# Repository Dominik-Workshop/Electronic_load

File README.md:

# DC Electronic load

### More info about this project can be found on my channel: 
 https://youtu.be/NScaRQj53l0

## Used tools:
 &nbsp;&nbsp;&nbsp;&nbsp; &nbsp;&nbsp;&nbsp;&nbsp; 
 &nbsp;&nbsp;&nbsp;&nbsp; &nbsp;&nbsp;&nbsp;&nbsp; 
 &nbsp;&nbsp; &nbsp;&nbsp;&nbsp;&nbsp; 

## Project status: :heavy_check_mark: ready for construction!
The project is poised for construction and operational use. However, ongoing development persists, addressing minor bug fixes and introducing new features. Stay tuned for updates!

## Project overview
Commercially available electronic loads often come with a hefty price tag, so I decided to build my own. 
This project was inspired by many electronic loads, with the primary inspiration being Scullcom's Electronic DC Load. You can view it [here](https://www.youtube.com/watch?v=9fsf1CgnTRk&list=PLUMG8JNssPPzbr4LydbTcBrhoPlemu5Dt&ab_channel=ScullcomHobbyElectronics).

&nbsp;&nbsp;&nbsp; 

### Project goals:
- **300 W power dissipation**

- **up to 8A and 50V** (obeying the 300W limit)

- **Remote voltage sensing option**

- **Easy to input values:** you can use an encoder as well as a keypad

- **5 modes of operation**
  - **Constant current mode**

  - **Constant power mode**

  - **Constant resistance mode**

  - **Transient response mode**

  - **Battery testing mode**

- **Nice to look at:** doesn't look like a poor DIY build

## Electronics:
### Block diagram

### PCBs:
- Main board: responsible for main funcionalities of the load

- Front board: responsible for user input with the rotary encoder and switching the voltage measurement circuitry between the main and sense terminals

## Mechanical construction:
The case for this project is made with 1mm thick bent sheet metal, with a 3D printed front panel.

## PC remote controll battery mode app
 
The app is currently available for Windows only. To run it, simply double-click on

`\desktop_app\release\windows-64bit\electronic_load_control_app.exe`

## Accuracy measurements
<details>
<summary>Click to learn more</summary>

The precision of the electronic load's current and voltage measurements, as well as its set current accuracy, were tested against the `Sanwa PC7000` multimeter. The following tables present the results of these measurements.

### Accuracy of set and measured current values

| Set Value [A] | Load Measurement [A] | Multimeter Measurement [A]  |
|:--------------|:---------------------|:----------------------------|
| 0.1           | 0.104                | 0.1032 ± 0.0029             |
| 0.2           | 0.203                | 0.2024 ± 0.0037             |
| 0.3           | 0.300                | 0.3000 ± 0.0044             |
| 0.4           | 0.406                | 0.4051 ± 0.0053             |
| 0.5           | 0.500                | 0.4997 ± 0.0060             |
| 0.6           | 0.602                | 0.6020 ± 0.0069             |
| 0.7           | 0.702                | 0.7020 ± 0.0077             |
| 0.8           | 0.800                | 0.8000 ± 0.0084             |
| 0.9           | 0.904                | 0.9038 ± 0.0093             |
| 1.0           | 1.007                | 1.0065 ± 0.0101             |
| 2.0           | 2.007                | 2.0070 ± 0.0181             |
| 3.0           | 3.006                | 3.0057 ± 0.0261             |
| 4.0           | 4.003                | 4.0022 ± 0.0341             |
| 5.0           | 5.002                | 5.0007 ± 0.0421             |
| 6.0           | 6.001                | 5.996 ± 0.068               |
| 7.0           | 6.998                | 6.997 ± 0.076               |
| 8.0           | 7.998                | 7.990 ± 0.084               |

### Accuracy of voltage measurements

| Load Measurement [V] | Multimeter Measurement [V] |
|:---------------------|:---------------------------|
| 1.002                | 1.0022 ± 0.0006            |
| 2.002                | 2.0029 ± 0.0009            |
| 3.004                | 3.0043 ± 0.0012            |
| 4.004                | 4.0039 ± 0.0015            |
| 5.006                | 5.0058 ± 0.0018            |
| 8.004                | 8.004 ± 0.006              |
| 10.01                | 10.007 ± 0.007             |
| 12.01                | 12.008 ± 0.007             |
| 14.01                | 14.010 ± 0.008             |
| 16.01                | 16.004 ± 0.009             |
| 18.01                | 18.007 ± 0.010             |
| 20.01                | 20.008 ± 0.011             |
| 25.01                | 25.011 ± 0.013             |
| 30.02                | 30.016 ± 0.015             |
| 35.02                | 35.019 ± 0.017             |
| 40.02                | 40.019 ± 0.019             |
| 45.02                | 45.023 ± 0.021             |
| 50.01                | 50.012 ± 0.023             |

### Conclusion: ✅

The current values measured by the electronic load did not deviate from the set value by more than **7 mA**. All measurements taken by the electronic load are within the range of values measured by the multimeter, considering the multimeter's measurement error.
</details>

## Uploading the code using USBASP
<details>
<summary>Click to learn more</summary>

Add the following code to the `platformio.ini` file

    upload_protocol = custom
    upload_port = usb
    upload_flags = 
        -C
        ${platformio.packages_dir}/tool-avrdude/avrdude.conf
        -p
        $BOARD_MCU
        -P
        $UPLOAD_PORT
        -c
        usbasp
    upload_command = avrdude $UPLOAD_FLAGS -U flash:w:$SOURCE:i

Uploading the code this way will reduce the boot up time.

**Note:** Since this method removes the bootloader, in order to program the uC via UART next time, you have to burn the bootloader.
</details>

## What could be improved in the next version:
  - Add reverse polarity protection
  - Higher resolution DAC

## Special thanks

Special thanks to [**Eryk Możdzeń**](https://github.com/Eryk-Mozdzen), who helped solving a software problem with a memory leak.

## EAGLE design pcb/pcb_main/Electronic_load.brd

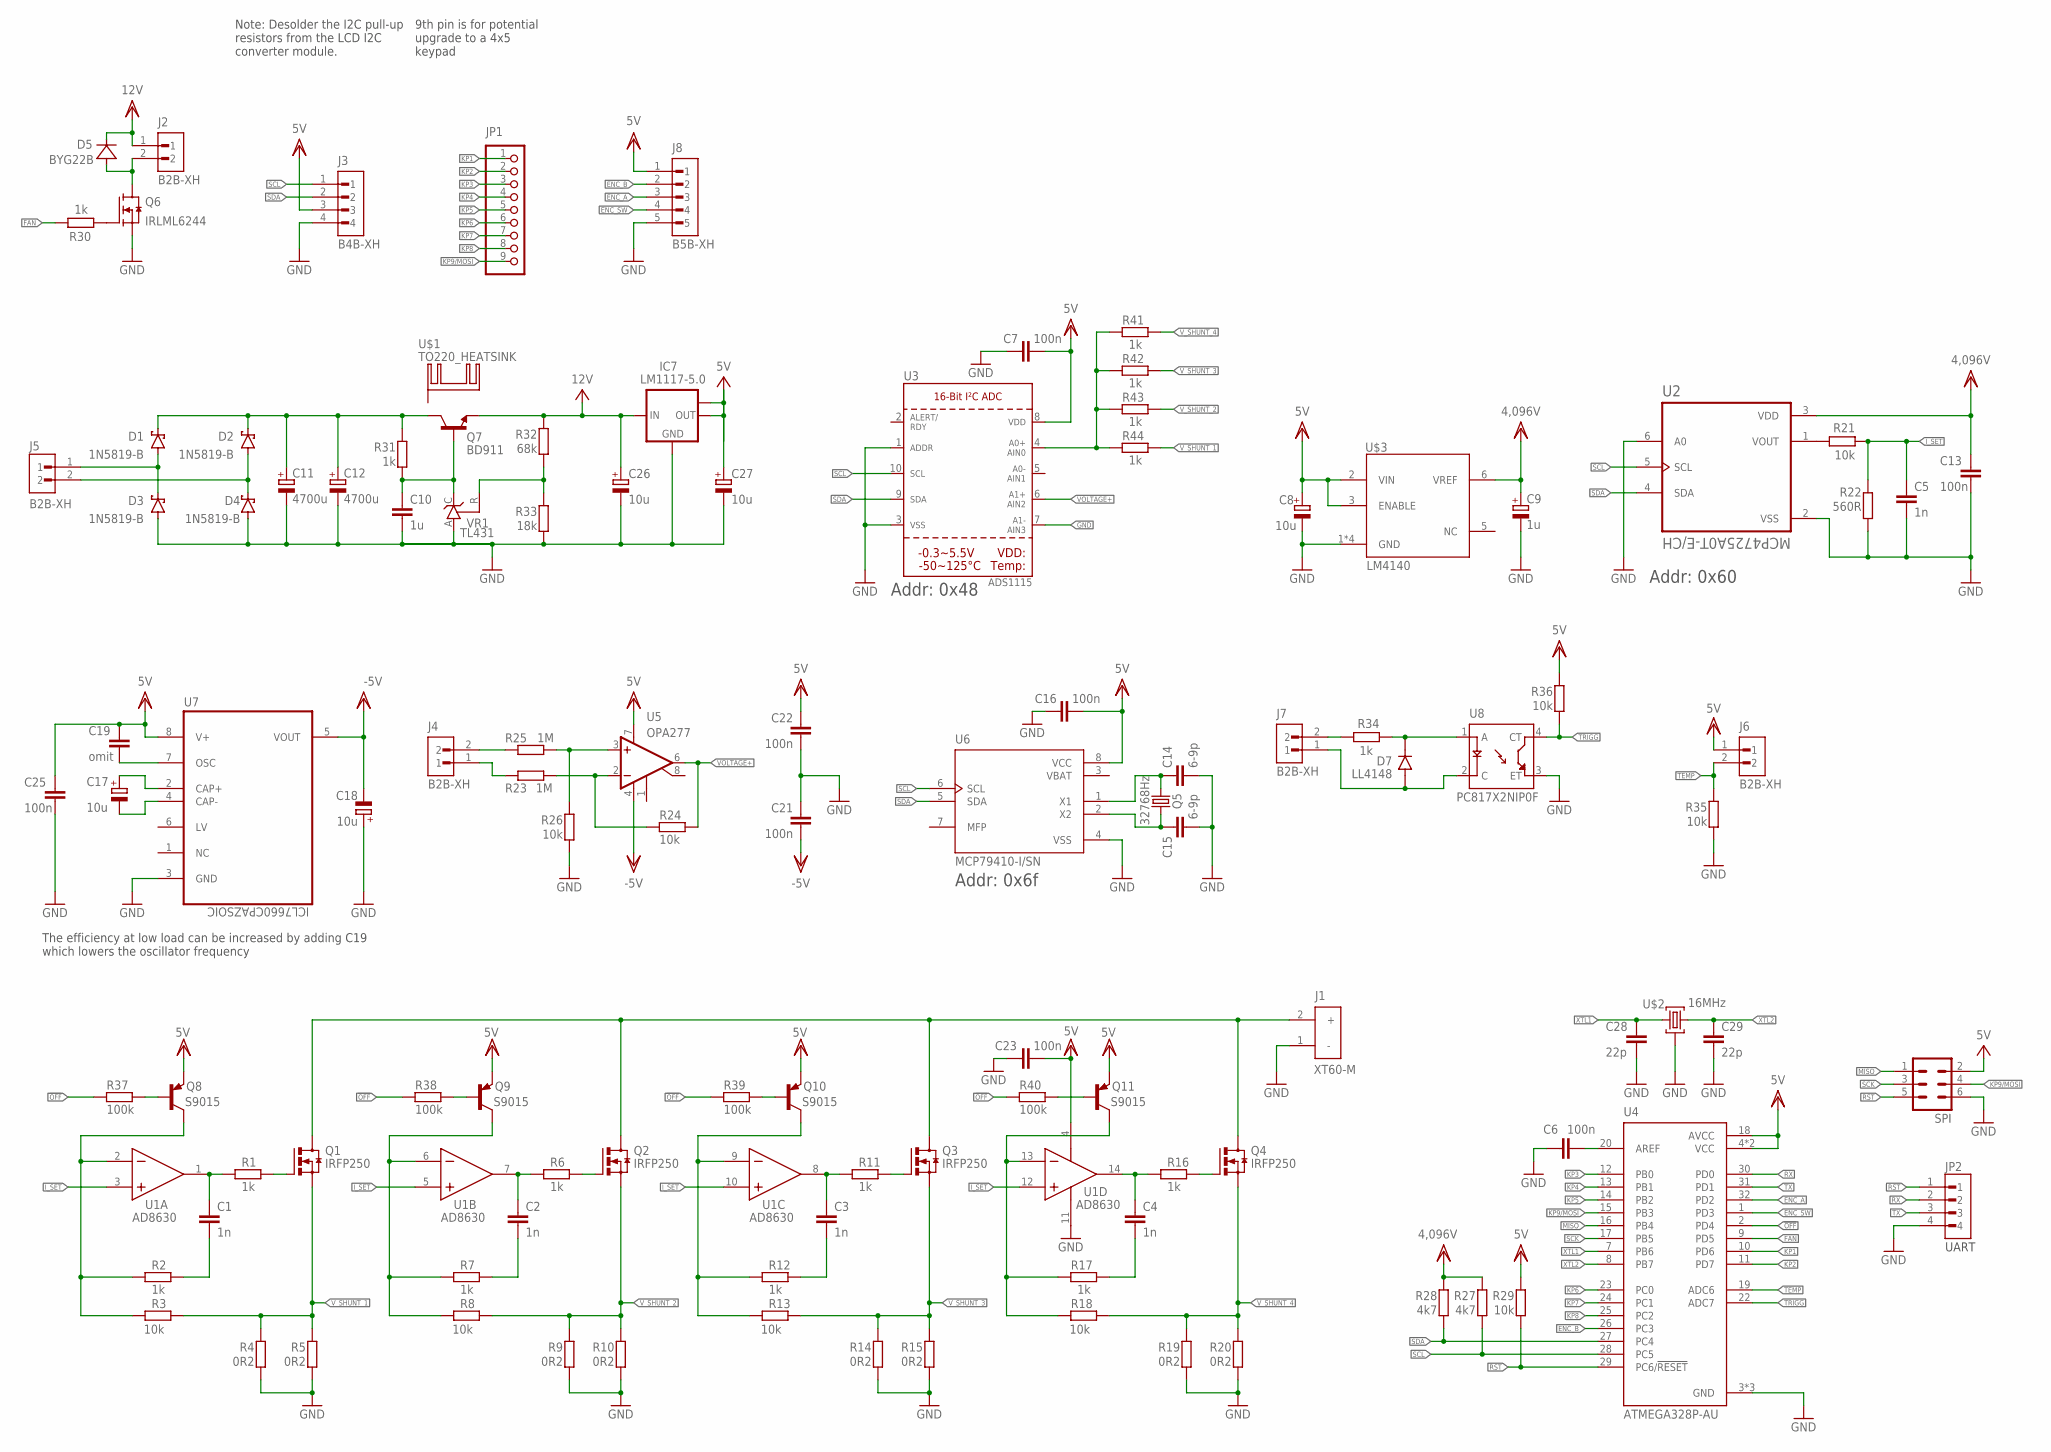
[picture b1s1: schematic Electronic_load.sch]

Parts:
C1, C2, C3, C4, C5: 1n; C0603
C6, C7, C13, C16, C21, C22, C25: 100n; C0603
C8, C17, C18: 10u; CT3528
C9: 1u; CT3216
C10: 1u; C0603
C11, C12: 4700u; E7,5-16
C14, C15: 6-9p; C0603
C19: omit; C0603
C23: 100n; C0603K
C26, C27: 10u; B/3528-21W
C28, C29: 22p; C0603
D1, D2, D3, D4: 1N5819-B; DO41-7.6
D5: BYG22B; DO-214AC
D7: LL4148; DIOMELF3515N
IC7: LM1117-5.0; SOT223
J1: XT60-M; AMASS_XT60-M
J2, J4, J5, J6, J7: B2B-XH; JST_B2B-XH-A(LF)(SN)
J3: B4B-XH; JST_B4B-XH-A(LF)(SN)
J8: B5B-XH; JST_B5B-XH-A(LF)(SN)
JP1: PINHD-1X9; 1X09
JP2: B4B-XH; JST_B4B-XH-A(LF)(SN)
Q1, Q2, Q3, Q4: IRFP250; TO-247AD-V
Q5: 32768Hz; TC26H
Q6: IRLML6244; SOT23
Q7: BD911; TO220V
Q8, Q9, Q10, Q11: S9015; SOT23
R1, R6, R11, R16, R31: 1k; R0805
R2, R7, R12, R17, R30, R34, R41, R42, R43, R44: 1k; R0603
R3, R8, R13, R18, R21, R24, R26, R29, R35, R36: 10k; R0603
R4, R5, R9, R10, R14, R15, R19, R20: 0R2; R4527
R22: 560R; R0603
R23, R25: 1M; R0603
R27, R28: 4k7; R0603
R32: 68k; R0603
R33: 18k; R0603
R37, R38, R39, R40: 100k; R0603
SPI: MA03-2
U1: ANALOG_DEVICES_AD8630ARZ-REEL7ANALOG_DEVICES_AD86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; ANALOG_DEVICES_AD8630ARZ-REEL7_0
U2: MCP4725A0T-E/CH; SOT95P270X145-6N
U3: ADS1115; MSOP10
U4: ATMEGA328P-AU; QFP80P900X900X120-32N
U5: OPA277; SOIC-08_150MIL
U6: MCP79410-I/SN; SOIC127P600X175-8N
U7: ICL7660CPAZSOIC; SOIC8
U8: PC817X2NIP0F; SOT254P975X400-4N
U$1: TO220_HEATSINK
U$2: 16MHz; CRYSTAL_3,4X2,7
U$3: LM4140; SOIC8
VR1: TL431; TO92-CLP

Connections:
4,096V: C9.+, C13.1, R27.1, R28.1, U2.3 (VDD), U$3.6 (VREF)
5V: C7.1, C8.+, C16.1, C19.1, C22.2, C23.1, C25.1, C27.+, IC7.2 (OUT), IC7.TAB (OUT1), J3.3, J6.1, J8.1, Q8.2 (E), Q9.2 (E), Q10.2 (E), Q11.2 (E), R29.1, R36.2, SPI.2, U1.4 (+V), U3.8 (VDD), U4.4 (VCC), U4.6 (VCC), U4.18 (AVCC), U5.7 (V+), U6.8 (VCC), U7.8 (V+), U$3.2 (VIN), U$3.3 (ENABLE)
12V: C26.+, D5.C, IC7.3 (IN), J2.1, Q7.3 (E), R32.1
16V: C11.+, C12.+, D1.C, D2.C, Q7.2 (C), R31.1
!OFF: R37.1, R38.1, R39.1, R40.1, U4.2 (PD4)
-5V: C18.-, C21.1, U5.4 (V-), U7.5 (VOUT)
AREF: C6.1, U4.20 (AREF)
BASE: C10.1, Q7.1 (B), R31.2, VR1.C
CURRENT: R41.1, R42.1, R43.1, R44.1, U3.4 (AIN0)
DAC_OUT: R21.2, U2.1 (VOUT)
ENC_A: J8.3, U4.32 (PD2)
ENC_B: J8.2, U4.26 (PC3)
ENC_SW: J8.4, U4.1 (PD3)
FAN: R30.1, U4.9 (PD5)
GND: C5.2, C6.2, C7.2, C8.-, C9.-, C10.2, C11.-, C12.-, C13.2, C14.2, C15.2, C16.2, C18.+, C21.2, C22.1, C23.2, C25.2, C26.-, C27.-, C28.2, C29.2, D3.A, D4.A, IC7.1 (GND), J1.1 (-), J3.4, J8.5, JP2.4, Q6.2 (S), R4.1, R5.1, R9.1, R10.1, R14.1, R15.1, R19.1, R20.1, R22.2, R26.1, R33.2, R35.1, SPI.6, U1.11 (-V), U2.2 (VSS), U2.6 (A0), U3.1 (ADDR), U3.3 (VSS), U3.7 (AIN3), U4.3 (GND), U4.5 (GND), U4.21 (GND), U6.4 (VSS), U7.3 (GND), U8.3 (ET), U$2.GND (2), U$2.GND2 (2), U$3.1 (GND), U$3.4 (GND), U$3.7 (GND), U$3.8 (GND), VR1.A
I_SET: C5.1, R21.1, R22.1, U1.3 (+IN_A), U1.5 (+IN_B), U1.10 (+IN_C), U1.12 (+IN_D)
KP1: JP1.1, U4.10 (PD6)
KP2: JP1.2, U4.11 (PD7)
KP3: JP1.3, U4.12 (PB0)
KP4: JP1.4, U4.13 (PB1)
KP5: JP1.5, U4.14 (PB2)
KP6: JP1.6, U4.23 (PC0)
KP7: JP1.7, U4.24 (PC1)
KP8: JP1.8, U4.25 (PC2)
KP9/MOSI: JP1.9, SPI.4, U4.15 (PB3)
MISO: SPI.1, U4.16 (PB4)
unnamed: D7.C (K), R34.1, U8.1 (A)
unnamed: R25.2, R26.2, U5.3 (+IN)
unnamed: C1.2, R2.2
unnamed: C1.1, R1.1, U1.1 (OUT_A)
unnamed: Q1.G, R1.2
unnamed: Q8.3 (C), R2.1, R3.2, U1.2 (-IN_A)
unnamed: J7.2, R34.2
unnamed: J1.2 (+), Q1.D, Q2.D, Q3.D, Q4.D
unnamed: C2.2, R7.2
unnamed: C2.1, R6.1, U1.7 (OUT_B)
unnamed: Q2.G, R6.2
unnamed: Q8.1 (B), R37.2
unnamed: Q9.3 (C), R7.1, R8.2, U1.6 (-IN_B)
unnamed: R23.2, R24.1, U5.2 (-IN)
unnamed: C3.2, R12.2
unnamed: C3.1, R11.1, U1.8 (OUT_C)
unnamed: Q3.G, R11.2
unnamed: Q10.3 (C), R12.1, R13.2, U1.9 (-IN_C)
unnamed: C4.2, R17.2
unnamed: C4.1, R16.1, U1.14 (OUT_D)
unnamed: Q4.G, R16.2
unnamed: Q11.3 (C), R17.1, R18.2, U1.13 (-IN_D)
unnamed: D5.A, J2.2, Q6.3 (D)
unnamed: J4.2, R25.1
unnamed: J4.1, R23.1
unnamed: D1.A, D3.C, J5.1
unnamed: D2.A, D4.C, J5.2
unnamed: Q6.1 (G), R30.2
unnamed: C17.+, U7.2 (CAP+)
unnamed: C17.-, U7.4 (CAP-)
unnamed: C14.1, Q5.2, U6.1 (X1)
unnamed: C15.1, Q5.1, U6.2 (X2)
unnamed: C19.2, U7.7 (OSC)
unnamed: Q9.1 (B), R38.2
unnamed: R32.2, R33.1, VR1.R
unnamed: Q10.1 (B), R39.2
unnamed: Q11.1 (B), R40.2
RST: JP2.1, R29.2, SPI.5, U4.29 (PC6/!RESET)
RX: JP2.2, U4.30 (PD0)
SCK: SPI.3, U4.17 (PB5)
SCL: J3.1, R27.2, U2.5 (SCL), U3.10 (SCL), U4.28 (PC5), U6.6 (SCL)
SDA: J3.2, R28.2, U2.4 (SDA), U3.9 (SDA), U4.27 (PC4), U6.5 (SDA)
TEMP: J6.2, R35.2, U4.19 (ADC6)
TRIGG: R36.1, U4.22 (ADC7), U8.4 (CT)
TX: JP2.3, U4.31 (PD1)
T_GND: D7.A, J7.1, U8.2 (C)
VBAT: U6.3 (VBAT)
VOLTAGE+: R24.2, U3.6 (AIN2), U5.6 (OUT)
V_SHUNT_1: Q1.S, R3.1, R4.2, R5.2, R44.2
V_SHUNT_2: Q2.S, R8.1, R9.2, R10.2, R43.2
V_SHUNT_3: Q3.S, R13.1, R14.2, R15.2, R42.2
V_SHUNT_4: Q4.S, R18.1, R19.2, R20.2, R41.2
XTL1: C28.1, U4.7 (PB6), U$2.CRST1 (1)
XTL2: C29.1, U4.8 (PB7), U$2.CRST2 (3)

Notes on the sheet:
Addr: 0x48
Addr: 0x60
Addr: 0x6f
The efficiency at low load can be increased by adding C19 which lowers the oscillator frequency
9th pin is for potential upgrade to a 4x5 keypad
UART
Note: Desolder the I2C pull-up resistors from the LCD I2C converter module.

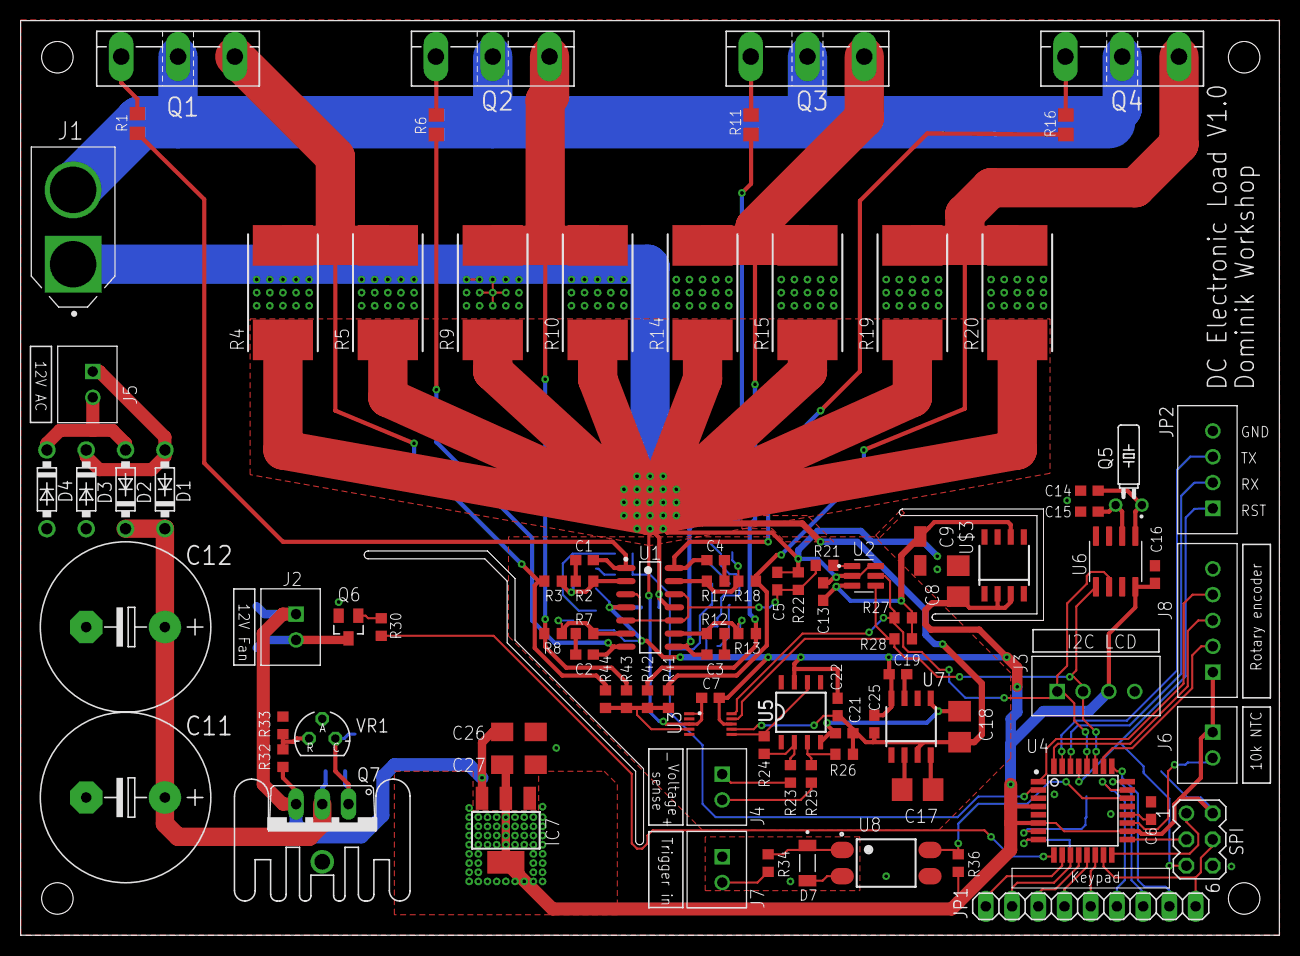
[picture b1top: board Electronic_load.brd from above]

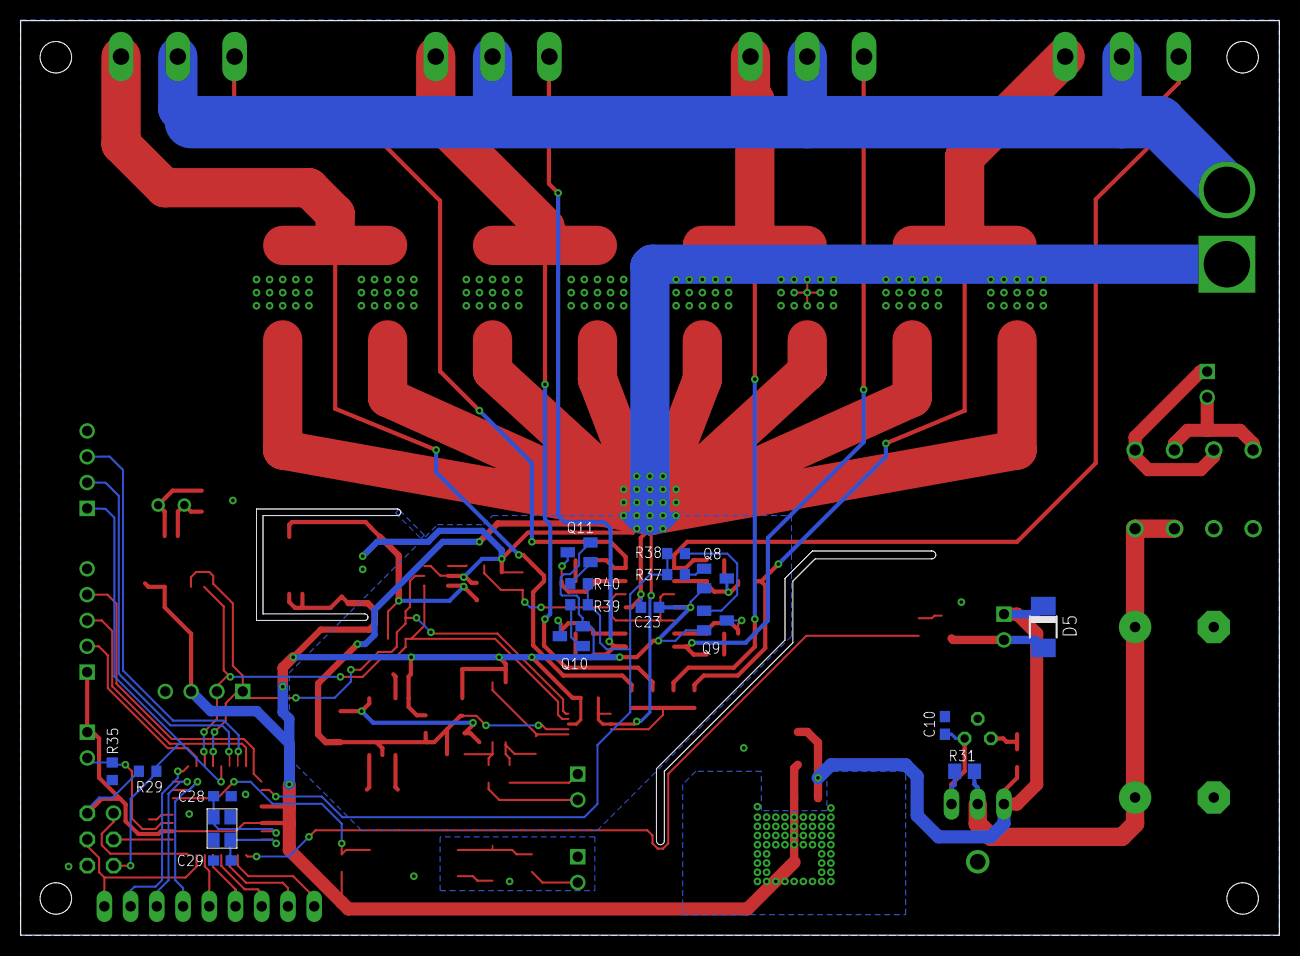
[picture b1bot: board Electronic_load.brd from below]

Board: 2 copper layers, 121.8 x 88.5 mm, 112 parts (17 on the bottom side), 79 nets.

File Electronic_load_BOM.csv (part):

"Part";"Value";"Device";"Package";"Description";"AMPLIFIERS_PER_PACKAGE";"AUTOMOTIVE_QUALIFIED";"AVAILABILITY";"CIIVA_IDS";"CODE__JEDEC";"COMPONENT_LINK_1_DESCRIPTION";"COMPONENT_LINK_1_URL";"COMPONENT_LINK_3_DESCRIPTION";"COMPONENT_LINK_3_URL";"DATASHEET";"DATASHEET_VERSION";"DESCRIPTION";"FOOTPRINT_VARIANT_NAME_0";"FOOTPRINT_VARIANT_NAME_1";"FOOTPRINT_VARIANT_NAME_2";"IMPORTED";"IMPORTED_FROM";"IMPORT_TS";"INPUT_BIAS_CURRENT";"INPUT_OFFSET_VOLTAGE";"IQ_AMP";"MF";"MOUNTING_TECHNOLOGY";"MP";"MPN";"OC_FARNELL";"OC_NEWARK";"PACKAGE";"PACKAGE_DESCRIPTION";"PACKAGE_VERSION";"POPULARITY";"PREFIX";"PRICE";"PURCHASE-URL";"RELEASE_DATE";"SLEW_RATE";"SMALL_SIGNAL_BANDWIDTH";"SPICEPREFIX";"VAULT_GUID";"VAULT_REVISION";"V_SPAN_MAX";"V_SPAN_MIN";
"C1";"1n";"C-EUC0603";"C0603";"CAPACITOR, European symbol";"";"";"";"";"";"";"";"";"";"";"";"";"";"";"";"";"";"";"";"";"";"";"";"";"";"";"";"";"";"";"73";"";"";"";"";"";"";"C";"";"";"";"";
"C2";"1n";"C-EUC0603";"C0603";"CAPACITOR, European symbol";"";"";"";"";"";"";"";"";"";"";"";"";"";"";"";"";"";"";"";"";"";"";"";"";"";"";"";"";"";"";"73";"";"";"";"";"";"";"C";"";"";"";"";
"C3";"1n";"C-EUC0603";"C0603";"CAPACITOR, European symbol";"";"";"";"";"";"";"";"";"";"";"";"";"";"";"";"";"";"";"";"";"";"";"";"";"";"";"";"";"";"";"73";"";"";"";"";"";"";"C";"";"";"";"";
"C4";"1n";"C-EUC0603";"C0603";"CAPACITOR, European symbol";"";"";"";"";"";"";"";"";"";"";"";"";"";"";"";"";"";"";"";"";"";"";"";"";"";"";"";"";"";"";"73";"";"";"";"";"";"";"C";"";"";"";"";
"C5";"1n";"C-EUC0603";"C0603";"CAPACITOR, European symbol";"";"";"";"";"";"";"";"";"";"";"";"";"";"";"";"";"";"";"";"";"";"";"";"";"";"";"";"";"";"";"73";"";"";"";"";"";"";"C";"";"";"";"";
"C6";"100n";"C-EUC0603";"C0603";"CAPACITOR, European symbol";"";"";"";"";"";"";"";"";"";"";"";"";"";"";"";"";"";"";"";"";"";"";"";"";"";"";"";"";"";"";"73";"";"";"";"";"";"";"C";"";"";"";"";
"C7";"100n";"C-EUC0603";"C0603";"CAPACITOR, European symbol";"";"";"";"";"";"";"";"";"";"";"";"";"";"";"";"";"";"";"";"";"";"";"";"";"";"";"";"";"";"";"73";"";"";"";"";"";"";"C";"";"";"";"";
"C8";"10u";"CPOL-EUCT3528";"CT3528";"POLARIZED CAPACITOR, European symbol";"";"";"";"";"";"";"";"";"";"";"";"";"";"";"";"";"";"";"";"";"";"";"";"";"";"";"";"";"";"";"1";"";"";"";"";"";"";"C";"";"";"";"";
"C9";"1u";"CPOL-EUCT3216";"CT3216";"POLARIZED CAPACITOR, European symbol";"";"";"";"";"";"";"";"";"";"";"";"";"";"";"";"";"";"";"";"";"";"";"";"";"";"";"";"";"";"";"1";"";"";"";"";"";"";"C";"";"";"";"";
"C10";"1u";"C-EUC0603";"C0603";"CAPACITOR, European symbol";"";"";"";"";"";"";"";"";"";"";"";"";"";"";"";"";"";"";"";"";"";"";"";"";"";"";"";"";"";"";"73";"";"";"";"";"";"";"C";"";"";"";"";
"C11";"4700u";"CPOL-EUE7.5-16";"E7,5-16";"POLARIZED CAPACITOR, European symbol";"";"";"";"";"";"";"";"";"";"";"";"";"";"";"";"";"";"";"";"";"";"";"";"";"";"";"";"";"";"";"4";"";"";"";"";"";"";"C";"";"";"";"";
"C12";"4700u";"CPOL-EUE7.5-16";"E7,5-16";"POLARIZED CAPACITOR, European symbol";"";"";"";"";"";"";"";"";"";"";"";"";"";"";"";"";"";"";"";"";"";"";"";"";"";"";"";"";"";"";"4";"";"";"";"";"";"";"C";"";"";"";"";
"C13";"100n";"C-EUC0603";"C0603";"CAPACITOR, European symbol";"";"";"";"";"";"";"";"";"";"";"";"";"";"";"";"";"";"";"";"";"";"";"";"";"";"";"";"";"";"";"73";"";"";"";"";"";"";"C";"";"";"";"";
"C14";"6-9p";"C-EUC0603";"C0603";"CAPACITOR, European symbol";"";"";"";"";"";"";"";"";"";"";"";"";"";"";"";"";"";"";"";"";"";"";"";"";"";"";"";"";"";"";"73";"";"";"";"";"";"";"C";"";"";"";"";
"C15";"6-9p";"C-EUC0603";"C0603";"CAPACITOR, European symbol";"";"";"";"";"";"";"";"";"";"";"";"";"";"";"";"";"";"";"";"";"";"";"";"";"";"";"";"";"";"";"73";"";"";"";"";"";"";"C";"";"";"";"";
"C16";"100n";"C-EUC0603";"C0603";"CAPACITOR, European symbol";"";"";"";"";"";"";"";"";"";"";"";"";"";"";"";"";"";"";"";"";"";"";"";"";"";"";"";"";"";"";"73";"";"";"";"";"";"";"C";"";"";"";"";
"C17";"10u";"CPOL-EUCT3528";"CT3528";"POLARIZED CAPACITOR, European symbol";"";"";"";"";"";"";"";"";"";"";"";"";"";"";"";"";"";"";"";"";"";"";"";"";"";"";"";"";"";"";"1";"";"";"";"";"";"";"C";"";"";"";"";
"C18";"10u";"CPOL-EUCT3528";"CT3528";"POLARIZED CAPACITOR, European symbol";"";"";"";"";"";"";"";"";"";"";"";"";"";"";"";"";"";"";"";"";"";"";"";"";"";"";"";"";"";"";"1";"";"";"";"";"";"";"C";"";"";"";"";
"C19";"omit";"C-EUC0603";"C0603";"CAPACITOR, European symbol";"";"";"";"";"";"";"";"";"";"";"";"";"";"";"";"";"";"";"";"";"";"";"";"";"";"";"";"";"";"";"73";"";"";"";"";"";"";"C";"";"";"";"";
"C21";"100n";"C-EUC0603";"C0603";"CAPACITOR, European symbol";"";"";"";"";"";"";"";"";"";"";"";"";"";"";"";"";"";"";"";"";"";"";"";"";"";"";"";"";"";"";"73";"";"";"";"";"";"";"C";"";"";"";"";
"C22";"100n";"C-EUC0603";"C0603";"CAPACITOR, European symbol";"";"";"";"";"";"";"";"";"";"";"";"";"";"";"";"";"";"";"";"";"";"";"";"";"";"";"";"";"";"";"73";"";"";"";"";"";"";"C";"";"";"";"";
"C23";"100n";"C-EUC0603K";"C0603K";"CAPACITOR, European symbol";"";"";"";"";"";"";"";"";"";"";"";"";"";"";"";"";"";"";"";"";"";"";"";"";"";"";"";"";"";"";"30";"";"";"";"";"";"";"C";"";"";"";"";
"C25";"100n";"C-EUC0603";"C0603";"CAPACITOR, European symbol";"";"";"";"";"";"";"";"";"";"";"";"";"";"";"";"";"";"";"";"";"";"";"";"";"";"";"";"";"";"";"73";"";"";"";"";"";"";"C";"";"";"";"";
"C26";"10u";"CPOL-EUB/3528-21W";"B/3528-21W";"POLARIZED CAPACITOR, European symbol";"";"";"";"";"";"";"";"";"";"";"";"";"";"";"";"";"";"";"";"";"";"";"";"";"";"";"";"";"";"";"4";"";"";"";"";"";"";"C";"";"";"";"";
"C27";"10u";"CPOL-EUB/3528-21W";"B/3528-21W";"POLARIZED CAPACITOR, European symbol";"";"";"";"";"";"";"";"";"";"";"";"";"";"";"";"";"";"";"";"";"";"";"";"";"";"";"";"";"";"";"4";"";"";"";"";"";"";"C";"";"";"";"";
"C28";"22p";"C-EUC0603";"C0603";"CAPACITOR, European symbol";"";"";"";"";"";"";"";"";"";"";"";"";"";"";"";"";"";"";"";"";"";"";"";"";"";"";"";"";"";"";"73";"";"";"";"";"";"";"C";"";"";"";"";
"C29";"22p";"C-EUC0603";"C0603";"CAPACITOR, European symbol";"";"";"";"";"";"";"";"";"";"";"";"";"";"";"";"";"";"";"";"";"";"";"";"";"";"";"";"";"";"";"73";"";"";"";"";"";"";"C";"";"";"";"";
"D1";"1N5819-B";"1N5819-B";"DO41-7.6";"1.0A SCHOTTKY BARRIER RECTIFIER";"";"";"";"";"";"";"";"";"";"";"";"";"";"";"";"";"";"";"";"";"";"";"";"";"";"";"";"";"";"";"11";"";"";"";"";"";"";"";"";"";"";"";
"D2";"1N5819-B";"1N5819-B";"DO41-7.6";"1.0A SCHOTTKY BARRIER RECTIFIER";"";"";"";"";"";"";"";"";"";"";"";"";"";"";"";"";"";"";"";"";"";"";"";"";"";"";"";"";"";"";"11";"";"";"";"";"";"";"";"";"";"";"";
"D3";"1N5819-B";"1N5819-B";"DO41-7.6";"1.0A SCHOTTKY BARRIER RECTIFIER";"";"";"";"";"";"";"";"";"";"";"";"";"";"";"";"";"";"";"";"";"";"";"";"";"";"";"";"";"";"";"11";"";"";"";"";"";"";"";"";"";"";"";
"D4";"1N5819-B";"1N5819-B";"DO41-7.6";"1.0A SCHOTTKY BARRIER RECTIFIER";"";"";"";"";"";"";"";"";"";"";"";"";"";"";"";"";"";"";"";"";"";"";"";"";"";"";"";"";"";"";"11";"";"";"";"";"";"";"";"";"";"";"";
"D5";"BYG22B";"BYG22B";"DO-214AC";"";"";"";"";"";"";"";"";"";"";"";"";"";"";"";"";"";"";"";"";"";"";"";"";"";"";"";"";"";"";"";"";"";"";"";"";"";"";"";"";"";"";"";
"D7";"LL4148";"LL4148";"DIOMELF3515N";"Check availability";"";"";"In Stock";"";"";"";"";"";"";"";"";" MMELF, 100V, 0.15A, Switching Diode & Array ";"";"";"";"";"";"";"";"";"";"Taiwan Semiconductor";"";"LL4148 L1";"";"";"";"MINI MELF-2 Taiwan Semiconductor";"";"";"";"";"None";"https://pricing.snapeda.com/search/part/LL4148 L1/?ref=eda";"";"";"";"";"";"";"";"";
"IC7";"LM1117IMPX-5.0";"LM1117IMPX-5.0";"SOT223";"";"";"";"";"";"";"";"";"";"";"";"";"";"";"";"";"";"";"";"";"";"";"";"";"";"";"";"";"";"";"";"";"";"";"";"";"";"";"";"";"";"";"";
"J1";"XT60-M";"XT60-M";"AMASS_XT60-M";"DC supply; XT60; male; PIN:2; for cable; soldered; 60A; 500V Check availability";"";"";"Not in stock";"";"";"";"";"";"";"";"";" Plug";" DC supply";" XT60";" male";" PIN: 2";" for cable";" soldered";" 30A";" 500V ";"";"";"";"";"";"";"";"";"";"AMASS";"";"XT60-M";"";"";"";"Package ";"";"";"";"";"None";"";
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
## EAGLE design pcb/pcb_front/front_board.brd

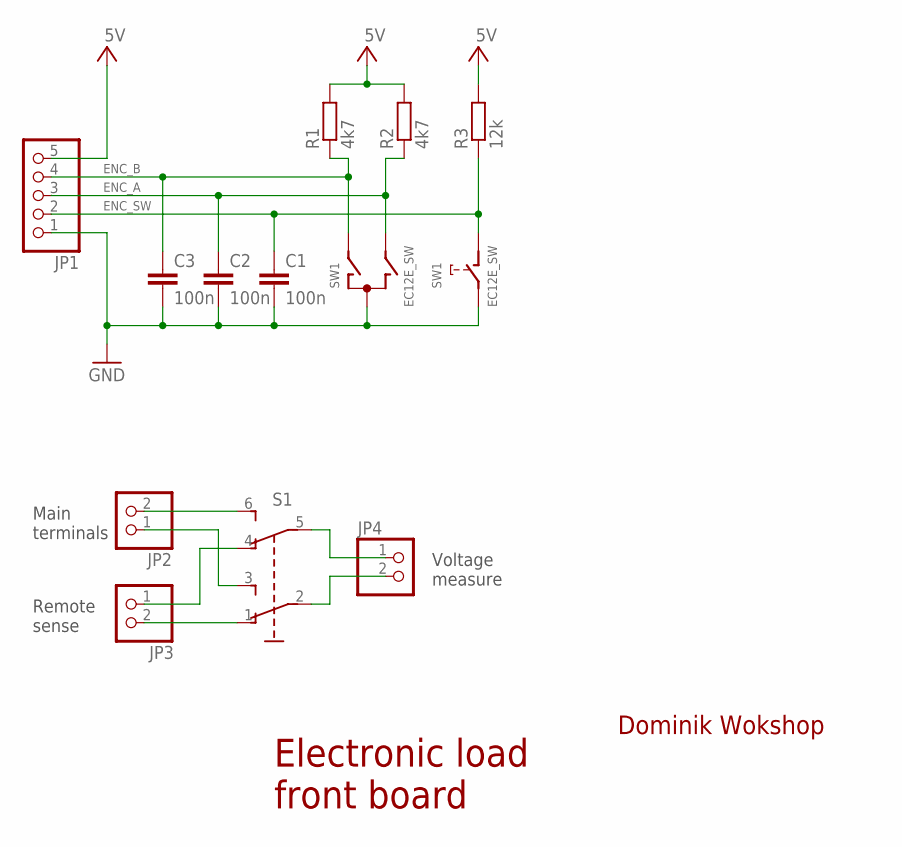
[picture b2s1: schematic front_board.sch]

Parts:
C1, C2, C3: 100n; C0603
JP1: PINHD-1X5/90; 1X05/90
JP2, JP3, JP4: PINHD-1X2/90; 1X02/90
R1, R2: 4k7; R0603
R3: 12k; R0603
S1: TL46PO; TL4XPO
SW1: EC12E_SW; ALPS_EC12E_SW

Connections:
5V: JP1.5, R1.2, R2.2, R3.2
ENC_A: C2.1, JP1.3, R2.1, SW1.B
ENC_B: C3.1, JP1.4, R1.1, SW1.A
ENC_SW: C1.1, JP1.2, R3.1, SW1.D (1)
GND: C1.2, C2.2, C3.2, JP1.1, SW1.C, SW1.E (2)
unnamed: JP4.2, S1.2
unnamed: JP3.2, S1.1 (O)
unnamed: JP4.1, S1.5 (P1)
unnamed: JP3.1, S1.4 (O1)
unnamed: JP2.1, S1.3 (S)
unnamed: JP2.2, S1.6 (S1)

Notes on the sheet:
Remote sense
Main terminals
Voltage measure
Electronic load front board
Dominik Wokshop

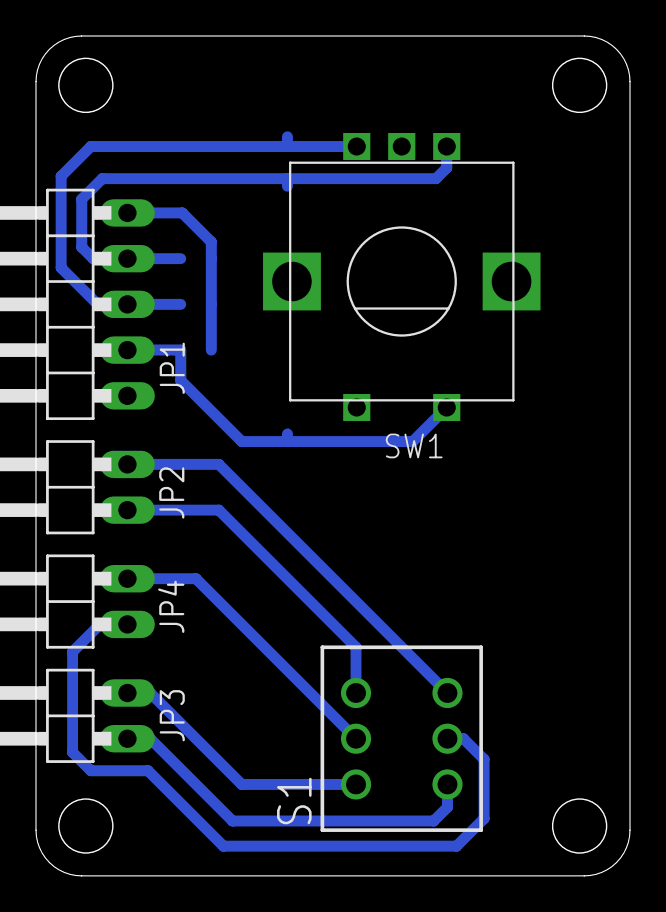
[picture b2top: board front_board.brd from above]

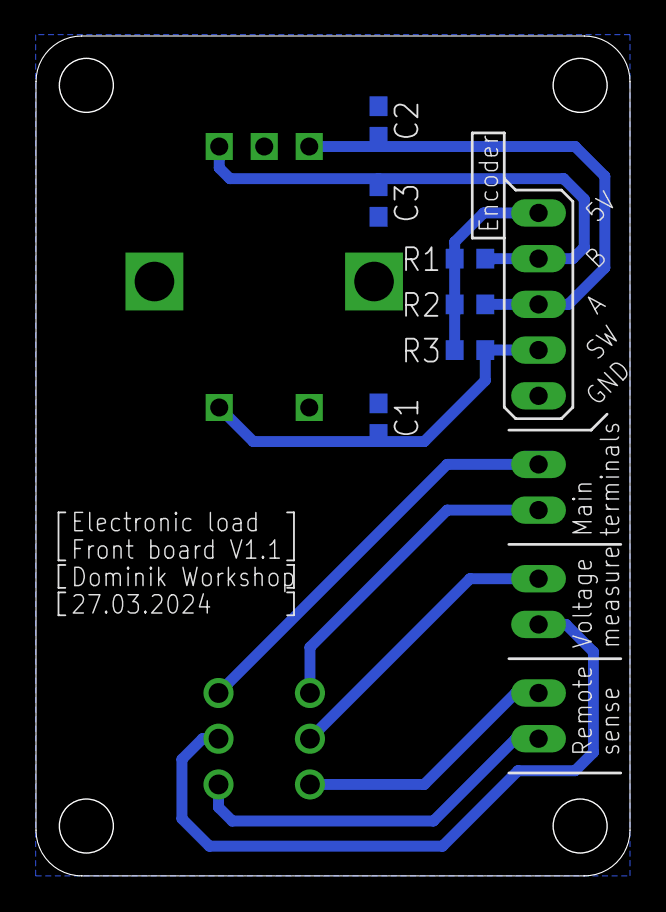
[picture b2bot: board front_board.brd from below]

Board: 2 copper layers, 32.9 x 46.6 mm, 12 parts (6 on the bottom side), 11 nets.

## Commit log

2022-07-12 datasheets
2022-07-12 VS Code initial commit
2022-07-12 ignore json
2022-07-12 most analog circutry done
2022-07-24 Power supply schematic done
2022-07-24 Most ICs
2022-07-24 Eagle trash
2022-07-24 Atmega pinout
2022-07-27 programming protocol via usbasp
2022-07-27 init function - pinMode
2022-07-27 calibration class and methods
2022-07-27 definition od pins and addresses
2022-07-27 initialized adc, dac, lcd, declared calValues
2022-07-27 finished power supply, added keypad, programming connector, transient trigger and more
2022-07-28 before voltage reference change
2022-07-29 new voltage reference
2022-07-31 finished V1.0
2022-07-31 added missing 3d models
2022-08-01 thermistor temperature measurement
2022-08-01 keypad, encoder, and thermistor
2022-08-01 encoder v1
2022-08-01 encoder init
2022-08-01 temperature and encoder test
2022-08-01 removed endoder init part
2022-08-01 encoder class with interrupt
2022-08-01 new encoder class tested
2022-08-01 methods definitions moved to source file
2022-08-01 9 pin keypad
2022-08-02 added encoder button
2022-08-02 encoder rotation and button tested
2022-08-03 keypad works
2022-08-04 finished V1
2022-08-05 new parts list
2022-08-05 added missing component values
2022-08-05 change value with encoder after key press
2022-08-05 degree and ohm custom character
2022-08-05 input value with decimal point from keypad
2022-08-05 fixed typo
2022-08-05 more comments
2022-08-05 user input class
2022-08-05 4 spaces -> 2 spaces indententions
2022-08-06 UserInput containing encoder and keypad
2022-08-06 seperate set variables, removed encoder and keypad
2022-08-06 enum with custom key names
2022-08-06 fixed some input bugs
2022-08-06 Encoder and Keypad separated from UserInput
2022-08-07 seperate function inputFromKeypad
2022-08-07 encoder switches decimal places
2022-08-07 display cursor pos (in resistance mode)
2022-08-07 UML diagram
2022-08-08 moving average filter
2022-08-08 constResistance new setting range
2022-08-08 all seems to work
2022-08-08 SetValue class
2022-08-08 max min value moved to private
2022-08-08 added values in description
2022-08-08 constPower and constResistance value input working
2022-08-09 removed numbers[] array
2022-08-09 minor imrovements
2022-08-17 added/corrected comments
2022-08-17 corrected comment
2022-08-19 changed encoder pin for pcb
2022-08-19 reversed encoder rotation
2022-08-19 changed for pcb
2022-08-20 datasheets update
2022-08-20 changed some resistor values
2022-08-23 cleaned up schematic
2022-08-28 License added
2022-08-29 test image
2022-08-29 first readme
2022-08-29 corrected image path
2022-08-29 rename folder
2022-08-29 renamed folder
2022-08-29 passed adc, dac objects
2022-08-29 template
2022-08-29 separate function for displaying the menu
2022-08-29 program via uart
2022-08-29 renders from fusion
2022-08-29 programming guidelines
2022-08-29 unfinished
2022-08-29 mount fits
2022-08-31 finished v1 printed
2022-09-02 painted and front finished
2022-09-02 height and holes adjusted
2022-09-02 project goals and to-do
2022-09-05 measurements work
2022-09-05 measurements in cons resistance
2022-09-05 updated to-do
2022-09-05 added comments
2022-09-06 lines counter
2022-09-06 none of the enums are zero
2022-09-06 decimal places enum
2022-09-06 CC mode, on/off, decimals enum
2022-09-06 on/off
2022-09-06 set current added
2022-09-06 dynamically change gain
2022-09-08 temperature moved to measurements
2022-09-08 temperature, calibration
2022-09-08 calibration, fan controll
2022-09-08 separate class for adc and dac calibration
2022-09-08 calibration, measurements
2022-09-08 offset current calibration
2022-09-08 getters and setters
2022-09-08 change displayed power precision >=100W
2022-09-08 zero current when off, (getters setters cal)
2022-09-08 more documentation, fanThreshold removed
2022-09-08 small renaming, dac getter setter
2022-09-08 EEPROM adresses renamed
2022-09-08 fan control, on/off
2022-09-09 enum min/max_decimal_place
2022-09-09 remove num_of_readings for mvng_average
2022-09-09 checkEncoder(), controlls
2022-09-09 adc moved to measurements
2022-09-09 controls class, power and resistance mode working
2022-09-09 load off on power up
2022-09-09 crude dac calibration
2022-09-09 dac offset cal
2022-09-09 description update
2022-09-09 timer library
2022-09-09 timer added
2022-09-09 cal, timer test
2022-09-09 current sink adjusted to new voltage divider
2022-09-09 power limiting test
2022-09-09 removed voltage parameter passed to functions
2022-09-09 removed measurements passed as parameter
2022-09-09 max values defines
2022-09-09 4mA min current
2022-09-09 dac offset calibration
2022-09-09 zero out current and power when load off
2022-09-10 update to-do, minor changes
2022-09-10 next version idea
2022-09-10 button debounce
2022-09-10 task loop
2022-09-10 documentation and clean up
2022-09-10 update readings when enetering via keypad
2022-09-11 minor changes
2022-09-11 rename current, power, resistance regulation func
2022-09-11 limit dacControll range, documentation
2022-09-11 documentation
2022-09-11 calibration finished
2022-09-11 clean up completed
2022-09-11 voltage with 3 decimals <10V
2022-09-12 began working on battery mode
2022-09-17 inputFromKeypad as userInput method works better
2022-09-18 checkEncoder as a method in userInput
2022-09-25 rotation doesn't print to lcd
2022-09-25 battery mode timer, encoder rotoration works
2022-09-25 added measured voltage offset calibration
2022-09-25 checkEncoder description
2022-09-25 keypad works in battery mode
2022-09-26 battery capacity measurement works
2022-09-26 cutoff edit, display capacity method
2022-09-27 cutoff works in battery mode
2022-09-27 capacity considering changes in current
2022-10-01 menu in void loop()
2022-10-01 debug2
2022-10-01 finally boots up
2022-10-01 doesn't run
2022-10-01 fix leak task
2022-10-01 int main() works
2022-10-01 works without void setup() and loop()
2022-10-01 FIXED MEMORY LEAK!!!!
2022-10-01 cleanup after debug and fix memory leak
2022-10-01 task done fix memory leak
2022-10-01 battery mode finished?
2022-10-02 transient continous works changing lowCurrent
2022-10-02 rename enum changed variable batt
2022-10-02 transient continous changing all variables works
2022-10-02 transient continous works
2022-10-02 battery and transient instances moved to main()
2022-10-02 toggling between set variables resets timer
2022-10-03 changedVariable enum moved to classes
2022-10-03 cleanup
2022-10-03 moved transient code to a method in the class
2022-10-03 pulse mode works
2022-10-05 added pictures
2022-10-05 fix max voltage
2022-10-13 schematic pdf
2022-11-18 updated class diagram
2022-11-28 better pictures
2022-12-02 cleaner constructor
2022-12-02 removed redundant break;
2022-12-23 init_value parameter
2023-02-10 encoder works great, bounces reduced
2023-02-10 shunt
2023-02-10 sticker
2023-02-28 disable calibration mode
2023-02-28 minor tweaks
2023-11-05 added C10, schematic minor updates
2023-11-05 pic with new keypad
2023-11-05 added YT link
2024-02-28 ign ini
2024-02-28 added tools logos
2024-02-28 minor adjustments
2024-03-27 align images
2024-03-27 gerber files
2024-03-27 rm bom
2024-04-03 communication works both ways
2024-04-04 cutoff voltage can be changed
2024-04-06 relocate sections
2024-04-06 not tested
2024-04-06 relocate sections, YT logo
2024-04-06 relocate section
2024-04-08 update R22 value
2024-04-17 new layout
2024-04-20 read changing parameters
2024-04-21 store voltage reagdinga
2024-04-21 try crc
2024-04-22 plot voltage, refactor
2024-05-27 change project structure
2024-05-28 save plots as jpg
2024-05-30 port selection works
2024-05-30 connection status messages
2024-05-30 calculate capacity in Wh
2024-05-30 add translations
2024-05-30 add translations combobox
2024-05-30 finish translations
2024-05-30 created settings window
2024-05-30 CRC works
2024-05-31 improve settings window
2024-05-31 change readings to a vector
2024-05-31 improve documentation
2024-05-31 minor improvements
2024-05-31 refactor, save to csv works
2024-05-31 ignore build folder
2024-06-01 small refactor
2024-06-01 rename variables
2024-06-01 add icon
2024-06-01 cleanup resources for icon
2024-06-02 remove settings window, menu bar added instead
2024-06-02 add german
2024-06-02 rename variable
2024-06-02 about message
2024-06-02 add lang folder
2024-06-02 add stopping when load is off option
2024-06-02 scaling plot from zero
2024-06-02 new icon, corrected receiving data
2024-06-02 add set parameters validator, correct
2024-06-02 PC app version alfa
2024-06-02 poormans rebase xd (im tired...)
2024-06-02 add generated documentation
2024-06-02 fix reset measurements, so it doesnt crash when clicked without serial connected
2024-06-03 minor measurement unit display fix, complete translations
2024-06-03 windows executable
2024-06-03 add missing files, should be good now
2024-06-06 improve frame layout and background color
2024-06-06 change vector to list
2024-06-06 add port connected indicator
2024-06-06 color of battery bar changes with percentage
2024-06-06 add separator bar in settings
2024-06-06 complete translations
2024-06-06 update documentation
2024-06-12 app beta
2024-06-12 remove junk
2024-06-12 working app
2024-06-13 ignore .pro.user
2024-06-13 fix text alignement, capacity digits
2024-06-13 update readme - desktop app
2024-06-13 update readme - used tools
2024-10-26 WIP: old changes
2024-10-26 Update project overview
2024-10-26 Add missing component designators on schematic, adjust text size and positioning
2024-10-26 Improve schematic, adjust text size and positioning
2024-11-04 Improve load renders
2024-11-05 Add more renders of the enclosure
2024-11-05 Remove capitalization of first letter in render images
2024-11-05 Improve PCB renders
2024-11-05 Ajust scale and positioning of front PCB render in README
2024-11-06 Fix typo in image name
2024-11-06 Improve schematic slightly
2024-11-20 Add electronics block diagram
2024-11-20 Convert electronics block diagram format to drawio.svg
2024-11-20 Add electronics block diagram to README
2024-11-21 Improve electronics block diagram
2024-11-30 Rename CURRENTx nets to V_SHUNT_x, add negation to OFF net on the main pcb
2024-11-30 Fix class diagram colors and convert to dravio.svg format
2024-12-18 Remove background from photos
2024-12-26 Add main PCB blend model
2024-12-26 Add drills to main PCB blend model
2024-12-26 Add correctly renamed gerber files necessary for blend generation
2025-02-25 Reverse calibration order: first offset then multiplier
2025-03-17 Add voltage and current accuracy measurements results to README
    Add voltage and current accuracy measurements results to README
